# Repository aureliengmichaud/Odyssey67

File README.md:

### Update: The PCB is now on Rev 2.1; it has been updated due to some minor clearance issues (stabilizers overlapping diodes). The plates are on Rev 2.0; two holes have been added for better support.

 A simple and practical 65% mechanical keyboard powered by the Elite-C microcontroller.

## Features

 * Simple and usable layout.
 * USB-C driven by the Elite-C microcontroller.
 * Awesome looking sandwich case.
 * No LEDs and no underglow.
 * Not another swiss cheese PCB.
 * Fully open source.
 * Powered by [QMK Firmware](https://github.com/qmk/qmk_firmware).

## Layout

### General Layout

### Keycaps Size Layout

## PCB

### Front

### Back

### Files

 Grab the zip containing the gerbers files needed for manufacturing [here](https://github.com/aureliengmichaud/Odyssey67/blob/master/Odyssey67-Gerbers-Rev21.zip). Simply upload the zip to the PCB manufacturer of your choice and off you go.

## Plates

### Switch Plate

### Bottom Plate

### Files

 Grab the files needed to get the plates made [here](https://github.com/aureliengmichaud/Odyssey67/tree/master/Plates). DXF and SVG files are included, depending on the manufacturer's needs.

## Parts List

 Part                                                                                                                                 |  Quantity
 :----------------------------------------------------------------------------------------------------------------------------------  |  :-------:
 [Odyssey 67 PCB](https://github.com/aureliengmichaud/Odyssey67/blob/master/Gerbers.zip)                                              |  1
 [1N4148 Diodes](https://candykeys.com/product/fairchild-semiconductor-diode-1n4148-pack-of-100)                                      |  67
 [Elite-C Microcontroller](https://splitkb.com/collections/keyboard-parts/products/elite-c-rev3-microcontroller)                      |  1
 [Cherry MX (or compatible) Switches](https://candykeys.com/category:switches/brand:cherry)                                           |  67
 [Cherry Stabilizers 2u](https://candykeys.com/product/original-cherry-2u-pcb-stabilizer)                                             |  3
 [Cherry Stabilizer 6.25u](https://candykeys.com/product/official-cherry-mx-stabiliser-6-25u)                                         |  1
 [Odyssey 67 Switch Plate](https://github.com/aureliengmichaud/Odyssey67/tree/master/Plates)                                          |  1
 [Odyssey 67 Bottom Plate](https://github.com/aureliengmichaud/Odyssey67/tree/master/Plates)                                          |  1
 [M3x8 Screws](https://www.ebay.fr/sch/i.html?_odkw=m3x8+screws&_osacat=0&_from=R40&_trksid=m570.l1313&_nkw=m3+screws&_sacat=0)       |  20
 [M3x14 Standoffs](https://www.ebay.fr/sch/i.html?_odkw=m3+screws&_osacat=0&_from=R40&_trksid=m570.l1313&_nkw=m3+standoffs&_sacat=0)  |  10
 [USB-C Cable](https://candykeys.com/product/black-nylon-usb-c-cable-1m)                                                              |  1
 [Keycaps](https://www.aliexpress.com/wholesale?catId=0&initiative_id=SB_20200426114303&SearchText=keycaps)                           |  67

## Build Guide

 If you're new to this, make sure to study and follow the build guide available [here](https://github.com/aureliengmichaud/Odyssey67/blob/master/BUILD_GUIDE.md).

## Firmware

 The keyboard is powered by [QMK Firmware](https://github.com/qmk/qmk_firmware). You can find the firmware for the Odyssey67 [here](https://github.com/aureliengmichaud/Odyssey67/tree/master/Firmware/aureliengmichaud/odyssey67).

 Add the `aureliengmichaud` folder to your own fork of QMK to flash it to your keyboard.

 If you're new to QMK, please take the time to learn all the ins and outs and familiarize yourself with it by reading the [official documentation](https://docs.qmk.fm/#/).

## License

 Released under [MIT License](https://github.com/aureliengmichaud/Odyssey67/blob/master/LICENSE).

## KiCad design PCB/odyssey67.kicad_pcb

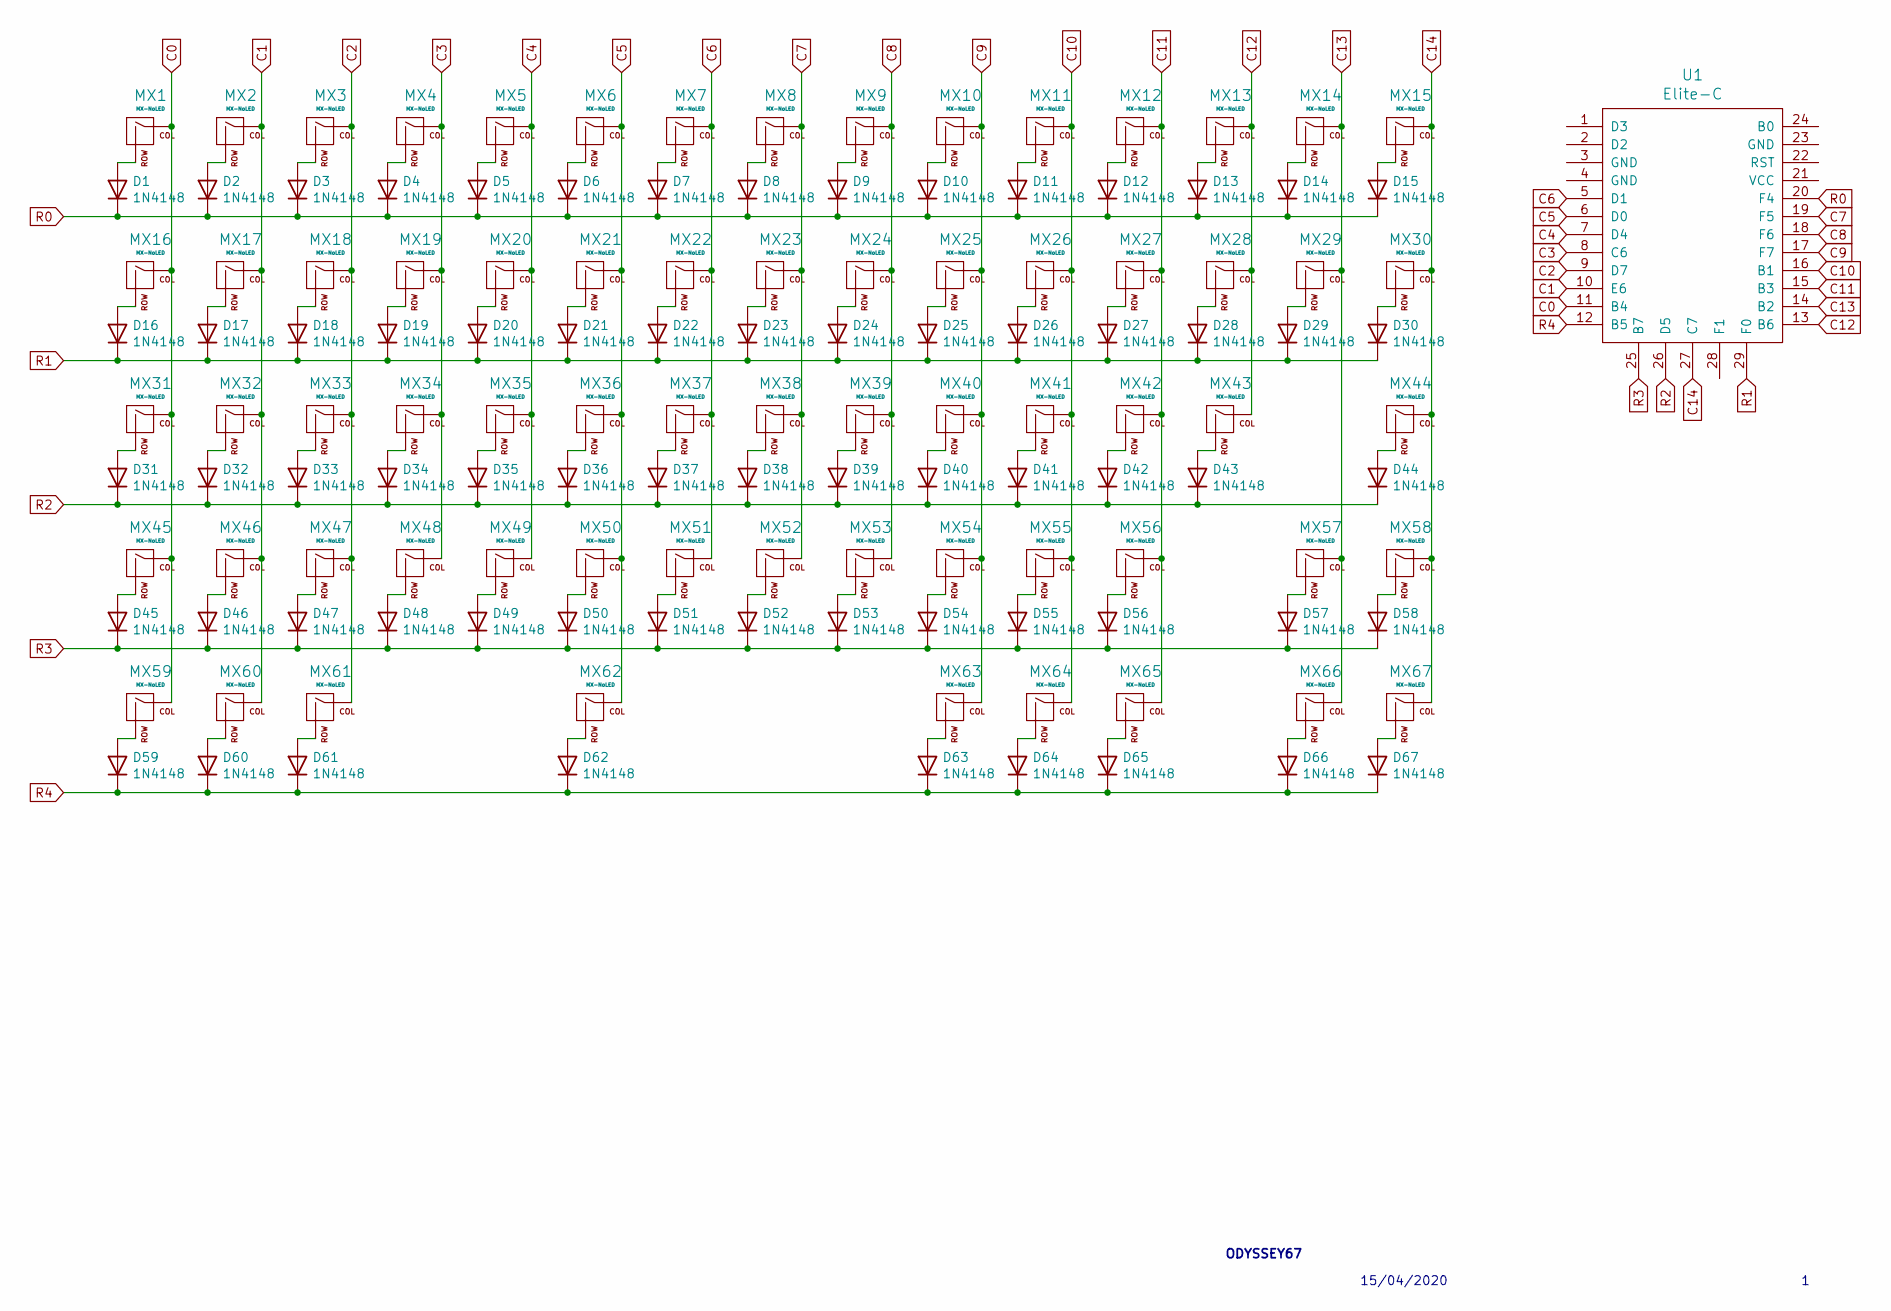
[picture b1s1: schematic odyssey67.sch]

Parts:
D1, D2, D3, D4, D5, D6, D7, D8, D9, D10, D11, D12, D13, D14, D15, D16, D17, D18, D19, D20, D21, D22, D23, D24, D25, D26, D27, D28, D29, D30, D31, D32, D33, D34, D35, D36, D37, D38, D39, D40, D41, D42, D43, D44, D45, D46, D47, D48, D49, D50, D51, D52, D53, D54, D55, D56, D57, D58, D59, D60, D61, D62, D63, D64, D65, D66, D67: 1N4148; D_DO-35_SOD27_P7.62mm_Horizontal
MX1, MX2, MX3, MX4, MX5, MX6, MX7, MX8, MX9, MX10, MX11, MX12, MX13, MX15, MX17, MX18, MX19, MX20, MX21, MX22, MX23, MX24, MX25, MX26, MX27, MX28, MX30, MX32, MX33, MX34, MX35, MX36, MX37, MX38, MX39, MX40, MX41, MX42, MX44, MX46, MX47, MX48, MX49, MX50, MX51, MX52, MX53, MX54, MX55, MX57, MX58, MX65, MX66, MX67: MX-NoLED; MXOnly-1U-NoLED
MX14: MX-NoLED; MXOnly-2U-NoLED
MX16, MX29, MX63, MX64: MX-NoLED; MXOnly-1.5U-NoLED
MX31, MX56: MX-NoLED; MXOnly-1.75U-NoLED
MX43, MX45: MX-NoLED; MXOnly-2.25U-NoLED
MX59, MX60, MX61: MX-NoLED; MXOnly-1.25U-NoLED
MX62: MX-NoLED; MXOnly-6.25U-NoLED
U1: Elite-C

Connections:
C0: MX1.1 (COL), MX16.1 (COL), MX31.1 (COL), MX45.1 (COL), MX59.1 (COL), U1.11 (B4)
C1: MX2.1 (COL), MX17.1 (COL), MX32.1 (COL), MX46.1 (COL), MX60.1 (COL), U1.10 (E6)
C2: MX3.1 (COL), MX18.1 (COL), MX33.1 (COL), MX47.1 (COL), MX61.1 (COL), U1.9 (D7)
C3: MX4.1 (COL), MX19.1 (COL), MX34.1 (COL), MX48.1 (COL), U1.8 (C6)
C4: MX5.1 (COL), MX20.1 (COL), MX35.1 (COL), MX49.1 (COL), U1.7 (D4)
C5: MX6.1 (COL), MX21.1 (COL), MX36.1 (COL), MX50.1 (COL), MX62.1 (COL), U1.6 (D0)
C6: MX7.1 (COL), MX22.1 (COL), MX37.1 (COL), MX51.1 (COL), U1.5 (D1)
C7: MX8.1 (COL), MX23.1 (COL), MX38.1 (COL), MX52.1 (COL), U1.19 (F5)
C8: MX9.1 (COL), MX24.1 (COL), MX39.1 (COL), MX53.1 (COL), U1.18 (F6)
C9: MX10.1 (COL), MX25.1 (COL), MX40.1 (COL), MX54.1 (COL), MX63.1 (COL), U1.17 (F7)
C10: MX11.1 (COL), MX26.1 (COL), MX41.1 (COL), MX55.1 (COL), MX64.1 (COL), U1.16 (B1)
C11: MX12.1 (COL), MX27.1 (COL), MX42.1 (COL), MX56.1 (COL), MX65.1 (COL), U1.15 (B3)
C12: MX13.1 (COL), MX28.1 (COL), MX43.1 (COL), U1.13 (B6)
C13: MX14.1 (COL), MX29.1 (COL), MX57.1 (COL), MX66.1 (COL), U1.14 (B2)
C14: MX15.1 (COL), MX30.1 (COL), MX44.1 (COL), MX58.1 (COL), MX67.1 (COL), U1.27 (C7)
unnamed: D1.2 (A), MX1.2 (ROW)
unnamed: D2.2 (A), MX2.2 (ROW)
unnamed: D3.2 (A), MX3.2 (ROW)
unnamed: D4.2 (A), MX4.2 (ROW)
unnamed: D5.2 (A), MX5.2 (ROW)
unnamed: D6.2 (A), MX6.2 (ROW)
unnamed: D7.2 (A), MX7.2 (ROW)
unnamed: D8.2 (A), MX8.2 (ROW)
unnamed: D9.2 (A), MX9.2 (ROW)
unnamed: D10.2 (A), MX10.2 (ROW)
unnamed: D11.2 (A), MX11.2 (ROW)
unnamed: D12.2 (A), MX12.2 (ROW)
unnamed: D13.2 (A), MX13.2 (ROW)
unnamed: D14.2 (A), MX14.2 (ROW)
unnamed: D15.2 (A), MX15.2 (ROW)
unnamed: D16.2 (A), MX16.2 (ROW)
unnamed: D17.2 (A), MX17.2 (ROW)
unnamed: D18.2 (A), MX18.2 (ROW)
unnamed: D19.2 (A), MX19.2 (ROW)
unnamed: D20.2 (A), MX20.2 (ROW)
unnamed: D21.2 (A), MX21.2 (ROW)
unnamed: D22.2 (A), MX22.2 (ROW)
unnamed: D23.2 (A), MX23.2 (ROW)
unnamed: D24.2 (A), MX24.2 (ROW)
unnamed: D25.2 (A), MX25.2 (ROW)
unnamed: D26.2 (A), MX26.2 (ROW)
unnamed: D27.2 (A), MX27.2 (ROW)
unnamed: D28.2 (A), MX28.2 (ROW)
unnamed: D29.2 (A), MX29.2 (ROW)
unnamed: D30.2 (A), MX30.2 (ROW)
unnamed: D31.2 (A), MX31.2 (ROW)
unnamed: D32.2 (A), MX32.2 (ROW)
unnamed: D33.2 (A), MX33.2 (ROW)
unnamed: D34.2 (A), MX34.2 (ROW)
unnamed: D35.2 (A), MX35.2 (ROW)
unnamed: D36.2 (A), MX36.2 (ROW)
unnamed: D37.2 (A), MX37.2 (ROW)
unnamed: D38.2 (A), MX38.2 (ROW)
unnamed: D39.2 (A), MX39.2 (ROW)
unnamed: D40.2 (A), MX40.2 (ROW)
unnamed: D41.2 (A), MX41.2 (ROW)
unnamed: D42.2 (A), MX42.2 (ROW)
unnamed: D43.2 (A), MX43.2 (ROW)
unnamed: D44.2 (A), MX44.2 (ROW)
unnamed: D45.2 (A), MX45.2 (ROW)
unnamed: D46.2 (A), MX46.2 (ROW)
unnamed: D47.2 (A), MX47.2 (ROW)
unnamed: D48.2 (A), MX48.2 (ROW)
unnamed: D49.2 (A), MX49.2 (ROW)
unnamed: D50.2 (A), MX50.2 (ROW)
unnamed: D51.2 (A), MX51.2 (ROW)
unnamed: D52.2 (A), MX52.2 (ROW)
unnamed: D53.2 (A), MX53.2 (ROW)
unnamed: D54.2 (A), MX54.2 (ROW)
unnamed: D55.2 (A), MX55.2 (ROW)
unnamed: D56.2 (A), MX56.2 (ROW)
unnamed: D57.2 (A), MX57.2 (ROW)
unnamed: D58.2 (A), MX58.2 (ROW)
unnamed: D59.2 (A), MX59.2 (ROW)
unnamed: D60.2 (A), MX60.2 (ROW)
unnamed: D61.2 (A), MX61.2 (ROW)
unnamed: D62.2 (A), MX62.2 (ROW)
unnamed: D63.2 (A), MX63.2 (ROW)
unnamed: D64.2 (A), MX64.2 (ROW)
unnamed: D65.2 (A), MX65.2 (ROW)
unnamed: D66.2 (A), MX66.2 (ROW)
unnamed: D67.2 (A), MX67.2 (ROW)
R0: D1.1 (K), D2.1 (K), D3.1 (K), D4.1 (K), D5.1 (K), D6.1 (K), D7.1 (K), D8.1 (K), D9.1 (K), D10.1 (K), D11.1 (K), D12.1 (K), D13.1 (K), D14.1 (K), D15.1 (K), U1.20 (F4)
R1: D16.1 (K), D17.1 (K), D18.1 (K), D19.1 (K), D20.1 (K), D21.1 (K), D22.1 (K), D23.1 (K), D24.1 (K), D25.1 (K), D26.1 (K), D27.1 (K), D28.1 (K), D29.1 (K), D30.1 (K), U1.29 (F0)
R2: D31.1 (K), D32.1 (K), D33.1 (K), D34.1 (K), D35.1 (K), D36.1 (K), D37.1 (K), D38.1 (K), D39.1 (K), D40.1 (K), D41.1 (K), D42.1 (K), D43.1 (K), D44.1 (K), U1.26 (D5)
R3: D45.1 (K), D46.1 (K), D47.1 (K), D48.1 (K), D49.1 (K), D50.1 (K), D51.1 (K), D52.1 (K), D53.1 (K), D54.1 (K), D55.1 (K), D56.1 (K), D57.1 (K), D58.1 (K), U1.25 (B7)
R4: D59.1 (K), D60.1 (K), D61.1 (K), D62.1 (K), D63.1 (K), D64.1 (K), D65.1 (K), D66.1 (K), D67.1 (K), U1.12 (B5)

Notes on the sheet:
ODYSSEY67
15/04/2020

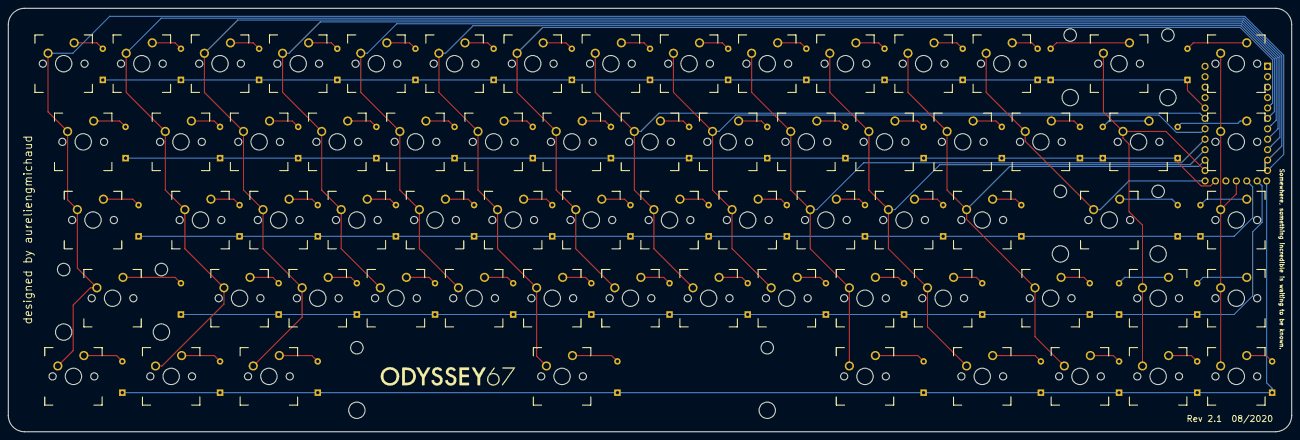
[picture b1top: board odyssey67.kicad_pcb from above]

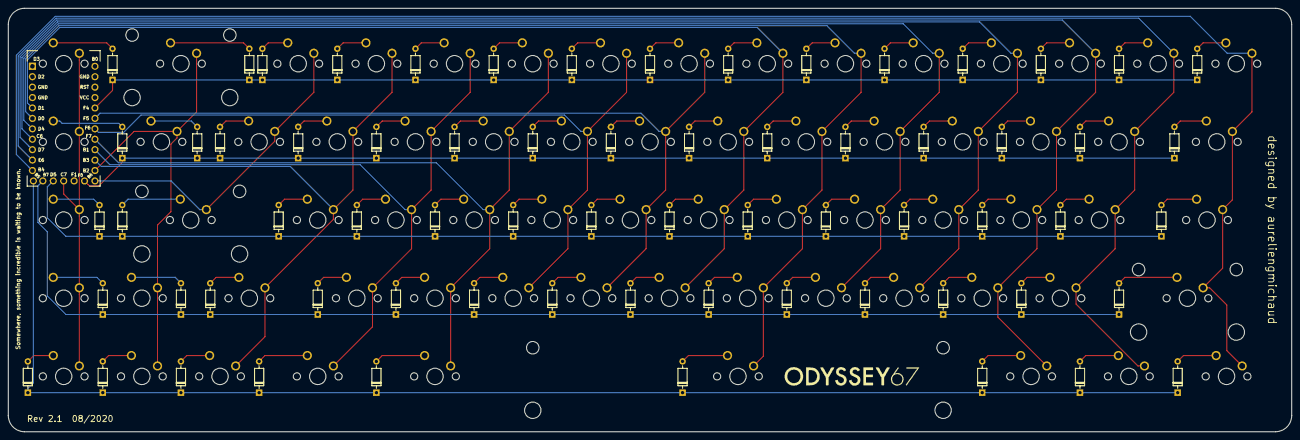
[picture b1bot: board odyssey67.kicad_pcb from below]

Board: 2 copper layers, 312.7 x 103.2 mm, 135 parts (68 on the bottom side), 87 nets.

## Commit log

2020-04-26 Add Images
2020-04-26 Add Plates
2020-04-26 Add PCB
2020-04-26 Create LICENSE
2020-04-26 Add PCB Render
2020-04-26 Update PCB Render
2020-04-26 Remove DS_Store
2020-04-26 Revert "Remove DS_Store"
    This reverts commit 3dab810dcee9d92b2b4182550d73bba18f56f46c.
2020-04-26 Update Plate & Case
2020-04-26 Update Build Guide
2020-04-26 Update Images
2020-04-26 Update Gerbers
2020-04-26 Update Plates
2020-05-06 Update Buld Guide
2020-05-17 Update PCB
2020-05-17 Add PCB Libraries
2020-05-26 Update PCB Libraries
2020-08-09 Updated PCB
2020-08-27 Update PCB / Plates
2020-09-14 Update Builde Guide
2021-02-21 PCB Libraries
2021-03-28 Add Firmware
2021-03-28 Update Firmware
2021-11-14 DS_Store
